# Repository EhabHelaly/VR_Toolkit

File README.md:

# VR Toolkit
An immersive yet affordable VR toolkit, for an application where user designs their dream houses as easy as thinking of it.
Project Description [here](https://drive.google.com/open?id=1B5nrhc0jkBZYwOeLX-Bp9c4Hi67hSx12).

Depanancies
===========
* OpenCV v3.1
* glew v1.13
* sdl v2.0

Hardware
========

* ATMEL AVR Micro controller
* ESP8266
* MPU6050
* HMC5883L
* IR light source
* 2 Cameras with IR Vision
* VR Box
* PC 

Supported Mobile Apps 
=====================
* https://play.google.com/store/apps/details?id=de.lorenz_fenster.sensorstreamgps&hl=en
* https://play.google.com/store/apps/details?id=udpcontroller.nomal&hl=en
* https://play.google.com/store/apps/details?id=com.kinoni.kinovrgear&hl=en

Sample images
=============

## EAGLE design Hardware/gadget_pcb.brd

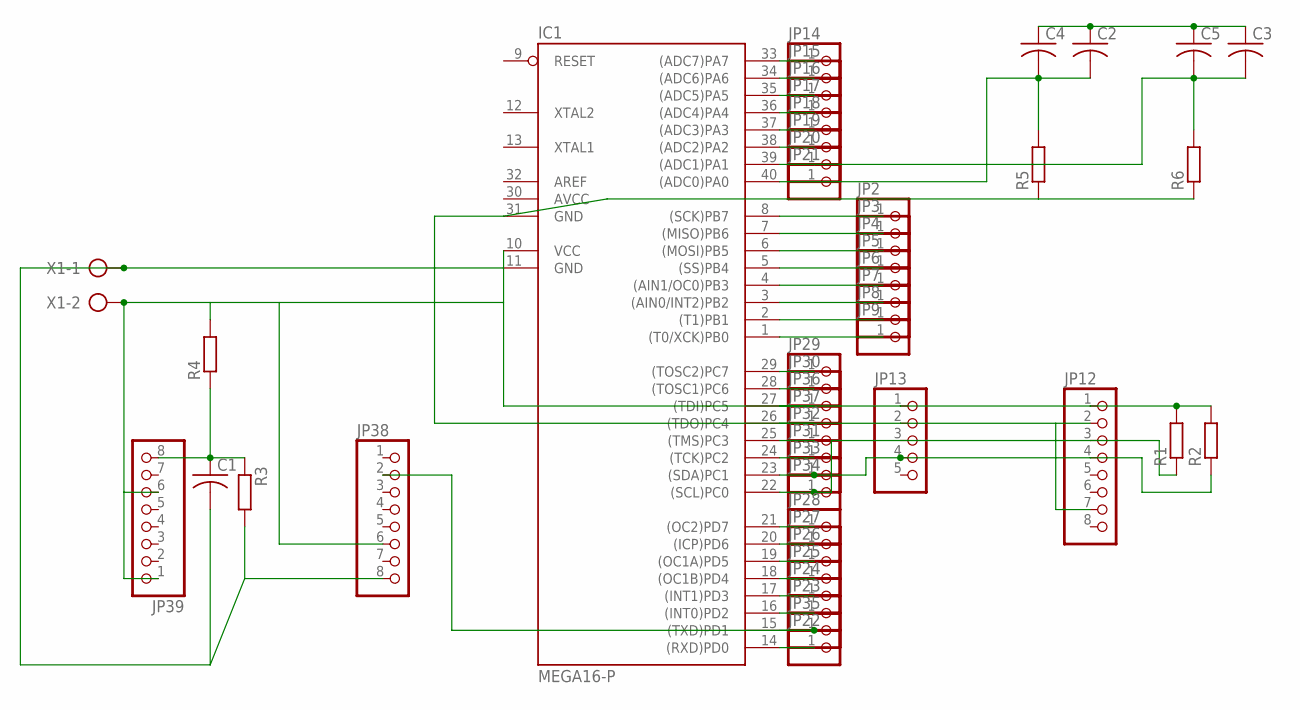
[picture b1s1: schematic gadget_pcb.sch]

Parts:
C1, C2, C3: C-US050-024X044; C050-024X044
C4, C5: C-US050-045X075; C050-045X075
IC1: MEGA16-P; DIL40
JP2, JP3, JP4, JP5, JP6, JP7, JP8, JP9, JP14, JP15, JP16, JP17, JP18, JP19, JP20, JP21, JP22, JP23, JP24, JP25, JP26, JP27, JP28, JP29, JP30, JP31, JP32, JP33, JP34, JP35, JP36, JP37: PINHD-1X1; 1X01
JP12, JP38, JP39: PINHD-1X8; 1X08
JP13: PINHD-1X5; 1X05
R1, R2, R4: R-EU_0207/10; 0207/10
R3: R-EU_0207/5V; 0207/5V
R5, R6: R-EU_0207/7; 0207/7
X1: AK500/2

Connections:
AVCC: IC1.30 (AVCC)
unnamed: IC1.27 ((TDI)PC5), JP36.1
unnamed: IC1.26 ((TDO)PC4), JP37.1
unnamed: IC1.15 ((TXD)PD1), JP35.1, JP38.2
unnamed: IC1.4 ((AIN1/OC0)PB3), JP6.1
unnamed: IC1.2 ((T1)PB1), JP8.1
unnamed: IC1.3 ((AIN0/INT2)PB2), JP7.1
unnamed: IC1.1 ((T0/XCK)PB0), JP9.1
unnamed: IC1.5 ((SS)PB4), JP5.1
unnamed: IC1.6 ((MOSI)PB5), JP4.1
unnamed: IC1.7 ((MISO)PB6), JP3.1
unnamed: IC1.8 ((SCK)PB7), JP2.1
unnamed: IC1.22 ((SCL)PC0), JP12.3, JP13.3, JP34.1, R1.1
unnamed: IC1.23 ((SDA)PC1), JP12.4, JP13.4, JP33.1, R2.1
unnamed: IC1.33 ((ADC7)PA7), JP14.1
unnamed: IC1.34 ((ADC6)PA6), JP15.1
unnamed: IC1.35 ((ADC5)PA5), JP16.1
unnamed: IC1.36 ((ADC4)PA4), JP17.1
unnamed: IC1.37 ((ADC3)PA3), JP18.1
unnamed: IC1.38 ((ADC2)PA2), JP19.1
unnamed: C3.2, C5.2, IC1.39 ((ADC1)PA1), JP20.1, R6.2
unnamed: C2.2, C4.2, IC1.40 ((ADC0)PA0), JP21.1, R5.2
unnamed: IC1.14 ((RXD)PD0), JP22.1
unnamed: IC1.16 ((INT0)PD2), JP23.1
unnamed: IC1.17 ((INT1)PD3), JP24.1
unnamed: IC1.18 ((OC1B)PD4), JP25.1
unnamed: IC1.19 ((OC1A)PD5), JP26.1
unnamed: IC1.20 ((ICP)PD6), JP27.1
unnamed: IC1.21 ((OC2)PD7), JP28.1
unnamed: IC1.29 ((TOSC2)PC7), JP29.1
unnamed: IC1.28 ((TOSC1)PC6), JP30.1
unnamed: IC1.24 ((TCK)PC2), JP31.1
unnamed: IC1.25 ((TMS)PC3), JP32.1
unnamed: IC1.10 (VCC), JP12.1, JP13.1, JP38.6, JP39.1, JP39.6, R1.2, R2.2, R4.2, X1.2
unnamed: C1.2, IC1.11 (GND), IC1.31 (GND), JP12.2, JP12.7, JP13.2, JP38.8, R3.2, R5.1, R6.1, X1.1
unnamed: C1.1, JP39.8, R3.1, R4.1
unnamed: C2.1, C3.1, C4.1, C5.1

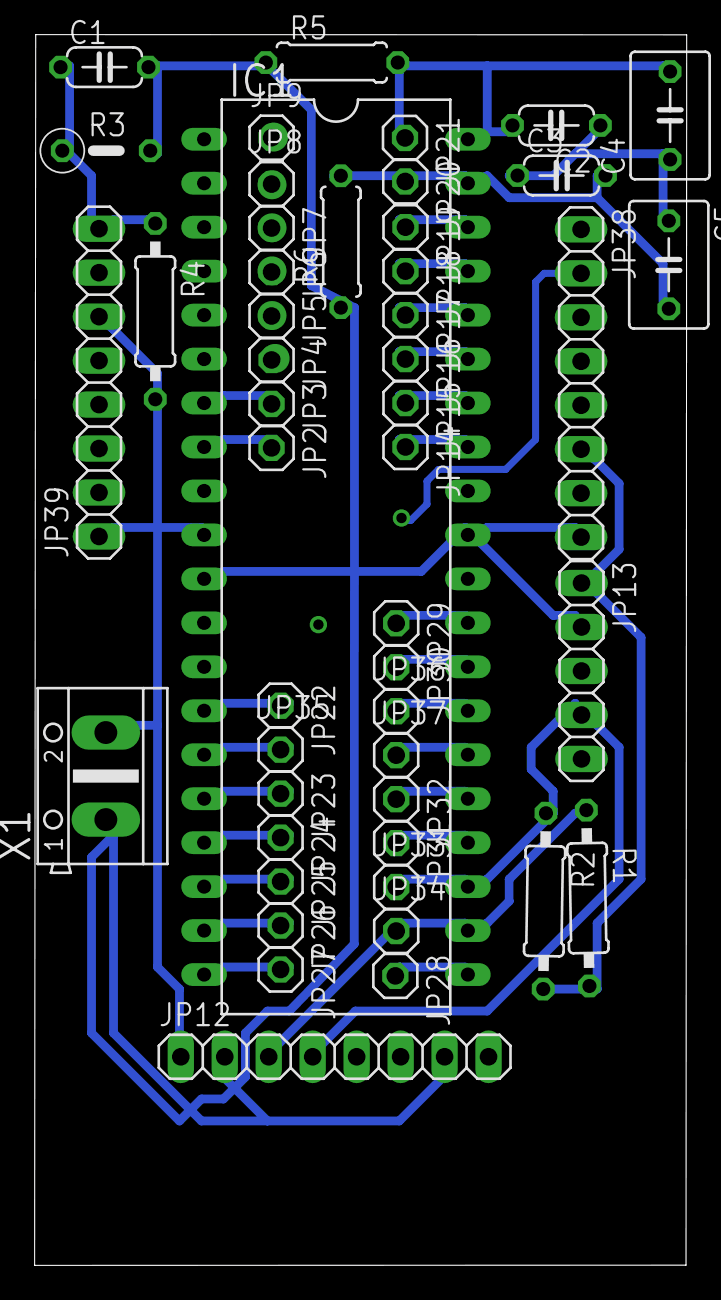
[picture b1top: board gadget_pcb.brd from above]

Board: 2 copper layers, 37.7 x 71.1 mm, 49 parts (0 on the bottom side), 36 nets.

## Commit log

2018-01-16 Project Files
2018-01-16 SS and Images
2018-01-16 interior designs
2018-01-16 Toolkit Projects
2018-01-16 VR App 3D Models
2018-01-18 Gadget PCB Hardware
2022-07-13 commit cbp files of tag v1.0.0
2022-07-13 add .gitignore
2022-07-13 add GameEngine.cbp project (excluding VR modules)
2022-07-13 overwrite main.scene on exit
2022-07-13 update light power exponent to be input to fragment shader
2022-07-13 correct model files paths to be relative + remove lastSession.scene
2022-07-13 show console message when model is loaded
